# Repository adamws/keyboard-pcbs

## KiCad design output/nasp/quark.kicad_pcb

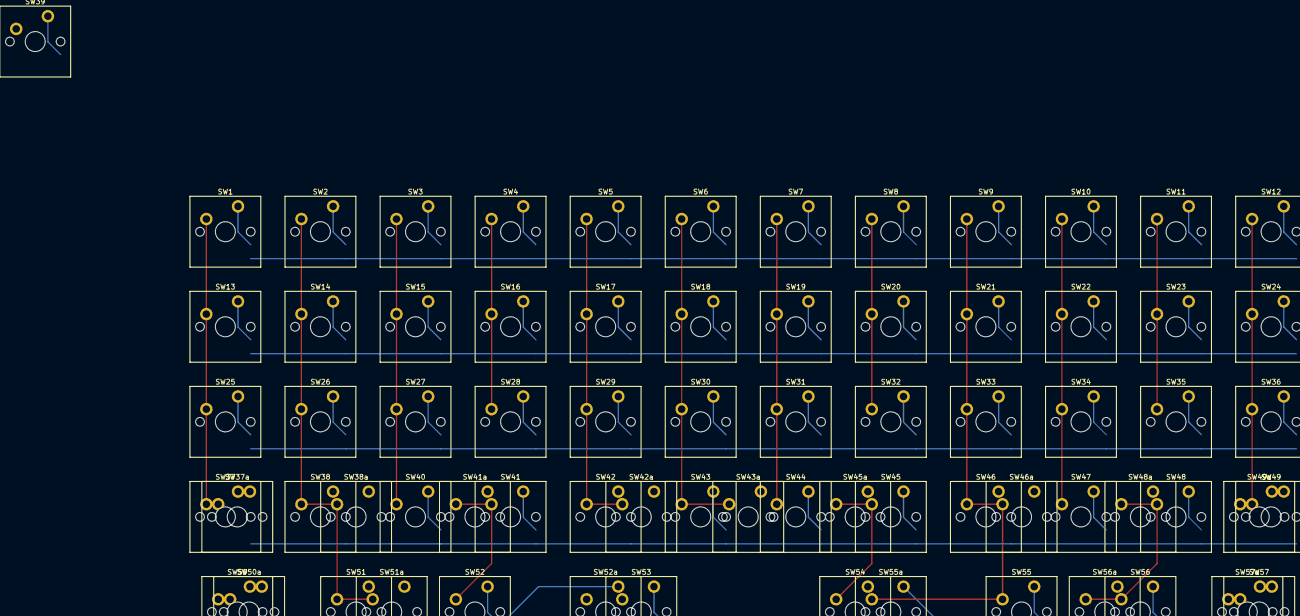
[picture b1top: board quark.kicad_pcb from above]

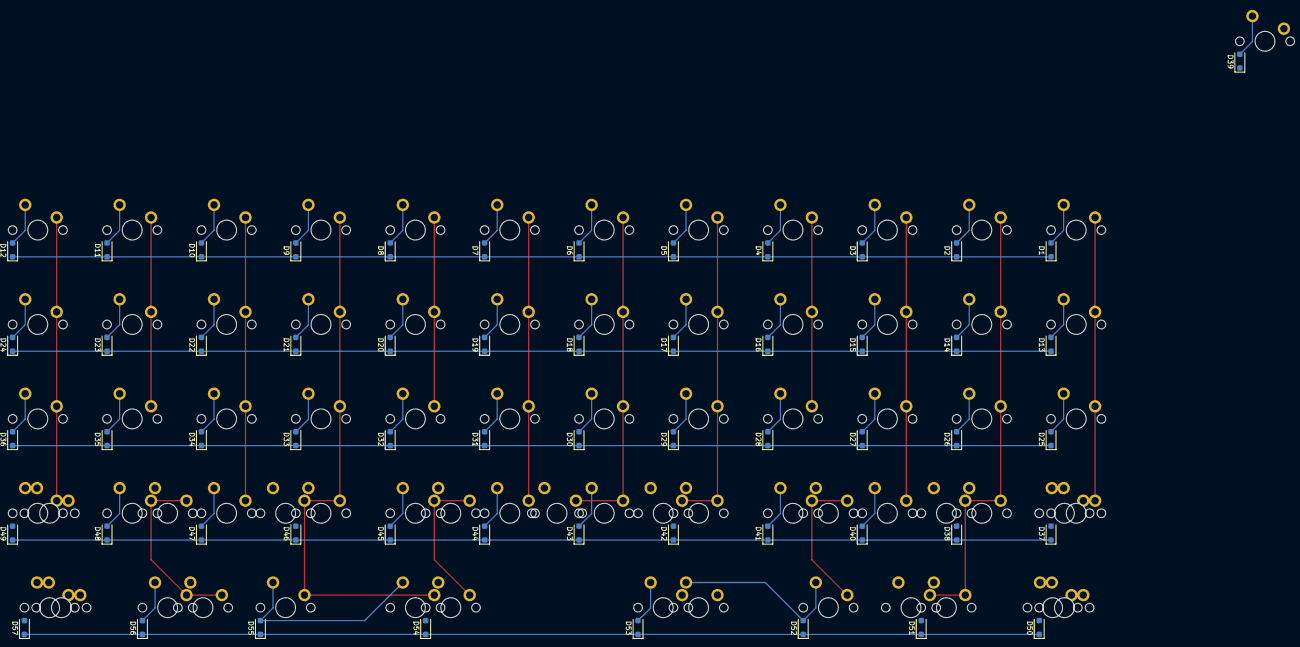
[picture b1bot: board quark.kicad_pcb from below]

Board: 2 copper layers, 129 parts (57 on the bottom side), 74 nets.

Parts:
D1, D2, D3, D4, D5, D6, D7, D8, D9, D10, D11, D12, D13, D14, D15, D16, D17, D18, D19, D20, D21, D22, D23, D24, D25, D26, D27, D28, D29, D30, D31, D32, D33, D34, D35, D36, D37, D38, D39, D40, D41, D42, D43, D44, D45, D46, D47, D48, D49, D50, D51, D52, D53, D54, D55, D56, D57: D_SOD-123F
SW1, SW2, SW3, SW4, SW5, SW6, SW7, SW8, SW9, SW10, SW11, SW12, SW13, SW14, SW15, SW16, SW17, SW18, SW19, SW20, SW21, SW22, SW23, SW24, SW25, SW26, SW27, SW28, SW29, SW30, SW31, SW32, SW33, SW34, SW35, SW36, SW37, SW37a, SW38, SW38a, SW39, SW40, SW41, SW41a, SW42, SW42a, SW43, SW43a, SW44, SW45, SW45a, SW46, SW46a, SW47, SW48, SW48a, SW49, SW49a, SW50, SW50a, SW51, SW51a, SW52, SW52a, SW53, SW54, SW55, SW55a, SW56, SW56a, SW57, SW57a: SW_Cherry_MX_PCB_1.00u

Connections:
COL0: SW1.1, SW13.1, SW25.1, SW37.1, SW37a.1, SW50.1, SW50a.1
COL1: SW2.1, SW14.1, SW26.1, SW38.1, SW38a.1, SW51.1, SW51a.1
COL2: SW3.1, SW15.1, SW27.1, SW40.1
COL3: SW4.1, SW16.1, SW28.1, SW41.1, SW41a.1, SW52.1, SW52a.1
COL4: SW5.1, SW17.1, SW29.1, SW42.1, SW42a.1, SW53.1
COL5: SW6.1, SW18.1, SW30.1, SW43.1, SW43a.1
COL6: SW7.1, SW19.1, SW31.1, SW44.1
COL7: SW8.1, SW20.1, SW32.1, SW45.1, SW45a.1, SW54.1
COL8: SW9.1, SW21.1, SW33.1, SW46.1, SW46a.1, SW55.1, SW55a.1
COL9: SW10.1, SW22.1, SW34.1, SW47.1
COL10: SW11.1, SW23.1, SW35.1, SW48.1, SW48a.1, SW56.1, SW56a.1
COL11: SW12.1, SW24.1, SW36.1, SW49.1, SW49a.1, SW57.1, SW57a.1
unnamed: D1.2, SW1.2
unnamed: D2.2, SW2.2
unnamed: D3.2, SW3.2
unnamed: D4.2, SW4.2
unnamed: D5.2, SW5.2
unnamed: D6.2, SW6.2
unnamed: D7.2, SW7.2
unnamed: D8.2, SW8.2
unnamed: D9.2, SW9.2
unnamed: D10.2, SW10.2
unnamed: D11.2, SW11.2
unnamed: D12.2, SW12.2
unnamed: D13.2, SW13.2
unnamed: D14.2, SW14.2
unnamed: D15.2, SW15.2
unnamed: D16.2, SW16.2
unnamed: D17.2, SW17.2
unnamed: D18.2, SW18.2
unnamed: D19.2, SW19.2
unnamed: D20.2, SW20.2
unnamed: D21.2, SW21.2
unnamed: D22.2, SW22.2
unnamed: D23.2, SW23.2
unnamed: D24.2, SW24.2
unnamed: D25.2, SW25.2
unnamed: D26.2, SW26.2
unnamed: D27.2, SW27.2
unnamed: D28.2, SW28.2
unnamed: D29.2, SW29.2
unnamed: D30.2, SW30.2
unnamed: D31.2, SW31.2
unnamed: D32.2, SW32.2
unnamed: D33.2, SW33.2
unnamed: D34.2, SW34.2
unnamed: D35.2, SW35.2
unnamed: D36.2, SW36.2
unnamed: D37.2, SW37.2, SW37a.2
unnamed: D38.2, SW38.2, SW38a.2
unnamed: D39.2, SW39.2
unnamed: D40.2, SW40.2
unnamed: D41.2, SW41.2, SW41a.2
unnamed: D42.2, SW42.2, SW42a.2
unnamed: D43.2, SW43.2, SW43a.2
unnamed: D44.2, SW44.2
unnamed: D45.2, SW45.2, SW45a.2
unnamed: D46.2, SW46.2, SW46a.2
unnamed: D47.2, SW47.2
unnamed: D48.2, SW48.2, SW48a.2
unnamed: D49.2, SW49.2, SW49a.2
unnamed: D50.2, SW50.2, SW50a.2
unnamed: D51.2, SW51.2, SW51a.2
unnamed: D52.2, SW52.2, SW52a.2
unnamed: D53.2, SW53.2
unnamed: D54.2, SW54.2
unnamed: D55.2, SW55.2, SW55a.2
unnamed: D56.2, SW56.2, SW56a.2
unnamed: D57.2, SW57.2, SW57a.2
ROW0: D1.1, D2.1, D3.1, D4.1, D5.1, D6.1, D7.1, D8.1, D9.1, D10.1, D11.1, D12.1
ROW1: D13.1, D14.1, D15.1, D16.1, D17.1, D18.1, D19.1, D20.1, D21.1, D22.1, D23.1, D24.1
ROW2: D25.1, D26.1, D27.1, D28.1, D29.1, D30.1, D31.1, D32.1, D33.1, D34.1, D35.1, D36.1
ROW3: D37.1, D38.1, D39.1, D40.1, D41.1, D42.1, D43.1, D44.1, D45.1, D46.1, D47.1, D48.1, D49.1
ROW4: D50.1, D51.1, D52.1, D53.1, D54.1, D55.1, D56.1, D57.1
